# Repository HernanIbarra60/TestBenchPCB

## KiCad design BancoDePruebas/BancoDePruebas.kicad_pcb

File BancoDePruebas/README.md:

# TestBenchPCB
This is a project to design a PCB for measuring the thrust force of a rocket engine.

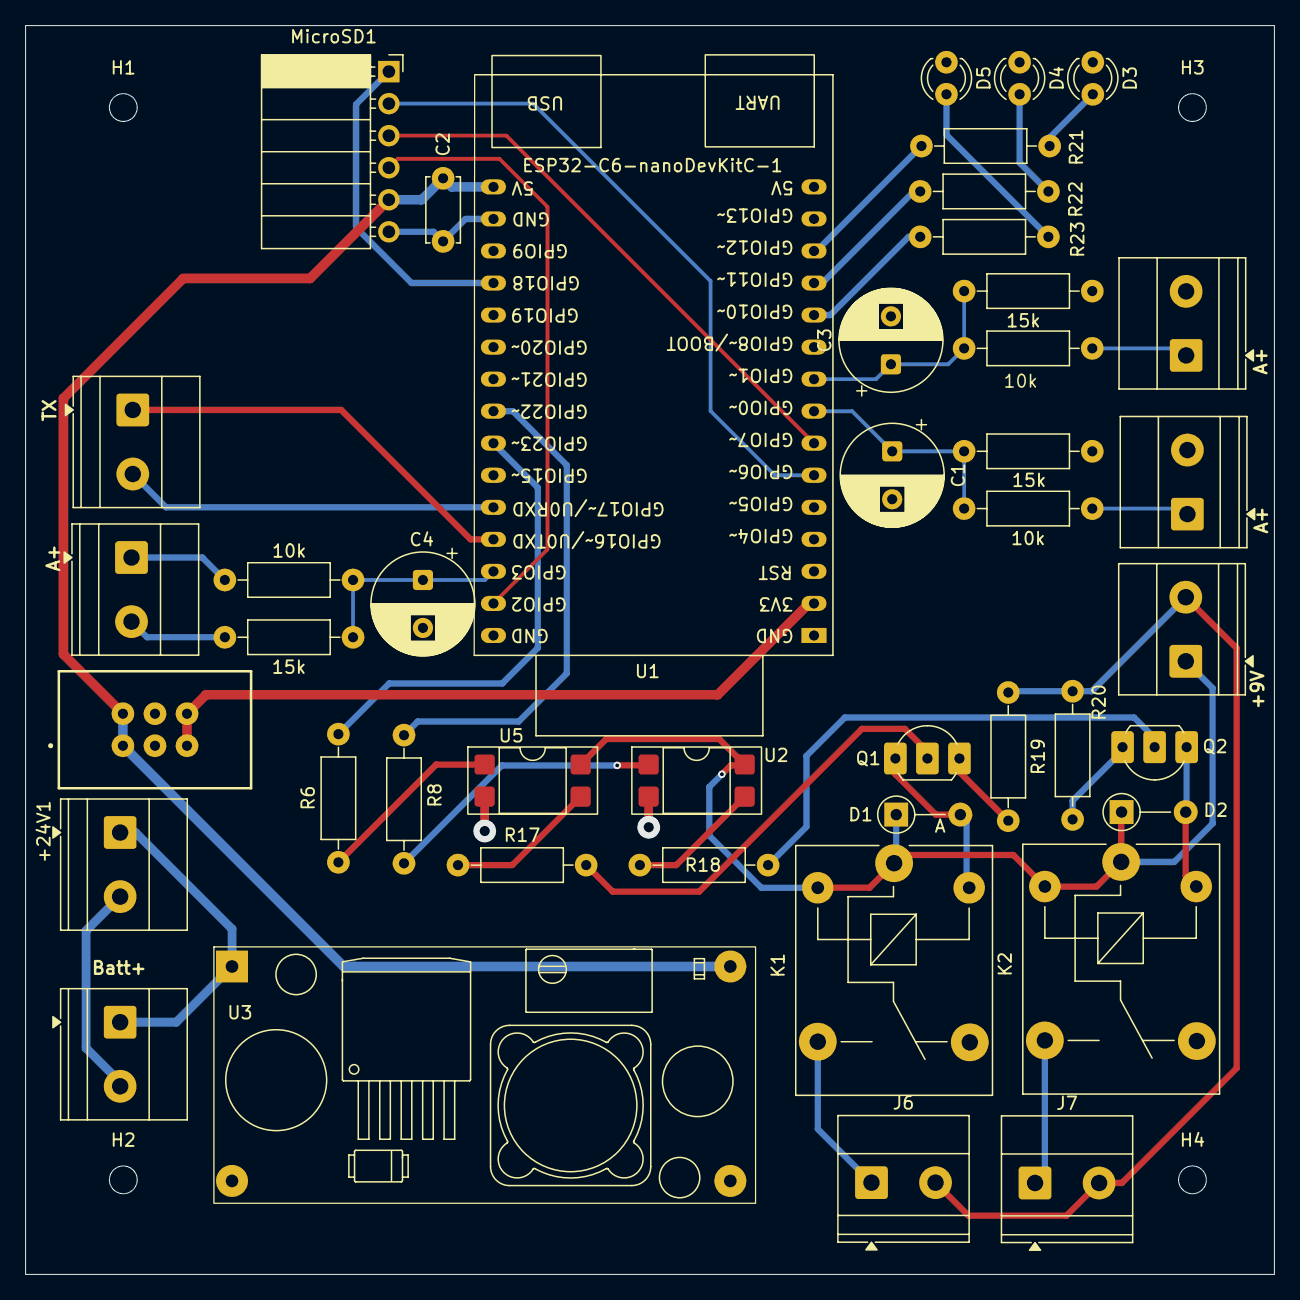
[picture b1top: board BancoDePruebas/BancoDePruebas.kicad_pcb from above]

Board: 2 copper layers, 99.0 x 99.0 mm, 47 parts (0 on the bottom side), 38 nets.

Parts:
10k, 10k#2, 10k#3: 10k; R_Axial_DIN0207_L6.3mm_D2.5mm_P10.16mm_Horizontal_Pad_0.8mm
15k, 15k#2, 15k#3: 15k; R_Axial_DIN0207_L6.3mm_D2.5mm_P10.16mm_Horizontal_Pad_0.8mm
+9V: Screw_Terminal_01x02; TerminalBlock_Phoenix_MKDS-1,5-2-5.08_1x02_P5.08mm_Horizont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
+24V1: BAT; TerminalBlock_Phoenix_MKDS-1,5-2-5.08_1x02_P5.08mm_Horizont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
A+: DAQ2; TerminalBlock_Phoenix_MKDS-1,5-2-5.08_1x02_P5.08mm_Horizont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
A+#2, A+#3: DAQ2; TerminalBlock_Phoenix_MKDS-1,5-2-5.08_1x02_P5.08mm_Horizont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
Batt+: BAT; TerminalBlock_Phoenix_MKDS-1,5-2-5.08_1x02_P5.08mm_Horizont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
C1, C3, C4: C_Polarized; CP_Radial_D8.0mm_P3.80mm
C2: 100nF; C_Disc_D5.0mm_W2.5mm_P5.00mm
D1, D2: D; D_A-405_P5.08mm_Vertical_AnodeUp_Pad_0.5mm
D3: S0; LED_D3.0mm_Pad_0.5mm
D4: S1; LED_D3.0mm_Pad_0.5mm
D5: S2; LED_D3.0mm_Pad_0.5mm
H1, H2, H3, H4: MountingHole; MountingHole_2.2mm_M2
J6: IGN1; TerminalBlock_Phoenix_MKDS-1,5-2-5.08_1x02_P5.08mm_Horizont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
J7: IGN2; TerminalBlock_Phoenix_MKDS-1,5-2-5.08_1x02_P5.08mm_Horizont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
K1, K2: SANYOU_SRD_IGN2; Relay_SPDT_SANYOU_SRD_Series_Form_C
MicroSD1: Conn_01x06; PinSocket_1x06_P2.54mm_Horizontal
Power_output1: Conn_02x03_Odd_Even; SAMTEC_TST-103-01-T-D
Q1, Q2: NPN; TO-92L_Inline_Wide_DIL_Pad
R6, R8: R; R_Axial_DIN0207_L6.3mm_D2.5mm_P10.16mm_Horizontal_Pad_0.8mm
R17, R18: 510; R_Axial_DIN0207_L6.3mm_D2.5mm_P10.16mm_Horizontal_Pad_0.8mm
R19, R20: 1.5; R_Axial_DIN0207_L6.3mm_D2.5mm_P10.16mm_Horizontal_Pad_0.8mm
R21, R22, R23: 220; R_Axial_DIN0207_L6.3mm_D2.5mm_P10.16mm_Horizontal_Pad_0.8mm
TX: DAQ2; TerminalBlock_Phoenix_MKDS-1,5-2-5.08_1x02_P5.08mm_Horizont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
U1: ESP32-C6-nanoDevKitC-1; ESP32-C6-nanoDevkit
U2, U5: PC817; DIP-4_W7.62mm_SMDSocket_SmallPads
U3: DCDC_StepDown_LM2596; YAAJ_DCDC_StepDown_LM2596_chinoka

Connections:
+3V3: Power_output1.5, Power_output1.6, U1.2 (3V3)
+5V: C2.1, MicroSD1.5, Power_output1.1, Power_output1.2, U1.30 (5V), U3.4 (Vout)
+9V: +9V.1, D1.1 (K), D2.1 (K), K1.1, K1.2, K2.1, K2.2, U2.4, U5.4
+BATT: +24V1.1, Batt+.1, U3.1 (Vin)
-BATT: 15k.2, 15k#2.2, 15k#3.2, +24V1.2, A+.2, A+#2.2, A+#3.2, Batt+.2, C1.2, C2.2, C3.2, C4.2, D3.1 (K), D4.1 (K), D5.1 (K), MicroSD1.6, Power_output1.3, Power_output1.4, U1.1 (GND), U1.16 (GND), U1.29 (GND), U2.2, U3.2 (GND), U3.3 (GND), U5.2
A1: 10k.2, 15k#2.1, C1.1, U1.8 (GPIO0)
A1_5v: 10k.1, A+#2.1
A2: 10k#2.2, 15k#3.1, C3.1, U1.9 (GPIO1)
A2_5v: 10k#2.1, A+.1
A3: 10k#3.2, 15k.1, C4.1, U1.18 (GPIO3)
A5_5v: 10k#3.1, A+#3.1
D0_IGN1: R6.1, U1.22 (GPIO23)
D1_IGN2: R8.1, U1.23 (GPIO22)
D2_S2: R23.1, U1.11 (GPIO10)
D3_S1: R22.1, U1.12 (GPIO11)
D4_S0: R21.1, U1.13 (GPIO12)
GND1: +9V.2, J6.2, J7.2, R19.1, R20.1
unnamed: D1.2 (A), K1.5, Q1.1 (C)
unnamed: D2.2 (A), K2.5, Q2.1 (C)
unnamed: D3.2 (A), R21.2
unnamed: D4.2 (A), R22.2
unnamed: D5.2 (A), R23.2
unnamed: J6.1, K1.3
unnamed: J7.1, K2.3
unnamed: Q1.2 (B), R17.2
unnamed: Q1.3 (E), R19.2
unnamed: Q2.2 (B), R18.2
unnamed: Q2.3 (E), R20.2
unnamed: R6.2, U5.1
unnamed: R8.2, U2.1
unnamed: R17.1, U5.3
unnamed: R18.1, U2.3
SPI_CS: MicroSD1.1, U1.27 (GPIO18)
SPI_MISO: MicroSD1.4, U1.17 (GPIO2)
SPI_MOSI: MicroSD1.3, U1.7 (GPIO7)
SPI_SCK: MicroSD1.2, U1.6 (GPIO6)
UART_RX: TX.2, U1.20 (GPIO17)
UART_TX: TX.1, U1.19 (GPIO16)

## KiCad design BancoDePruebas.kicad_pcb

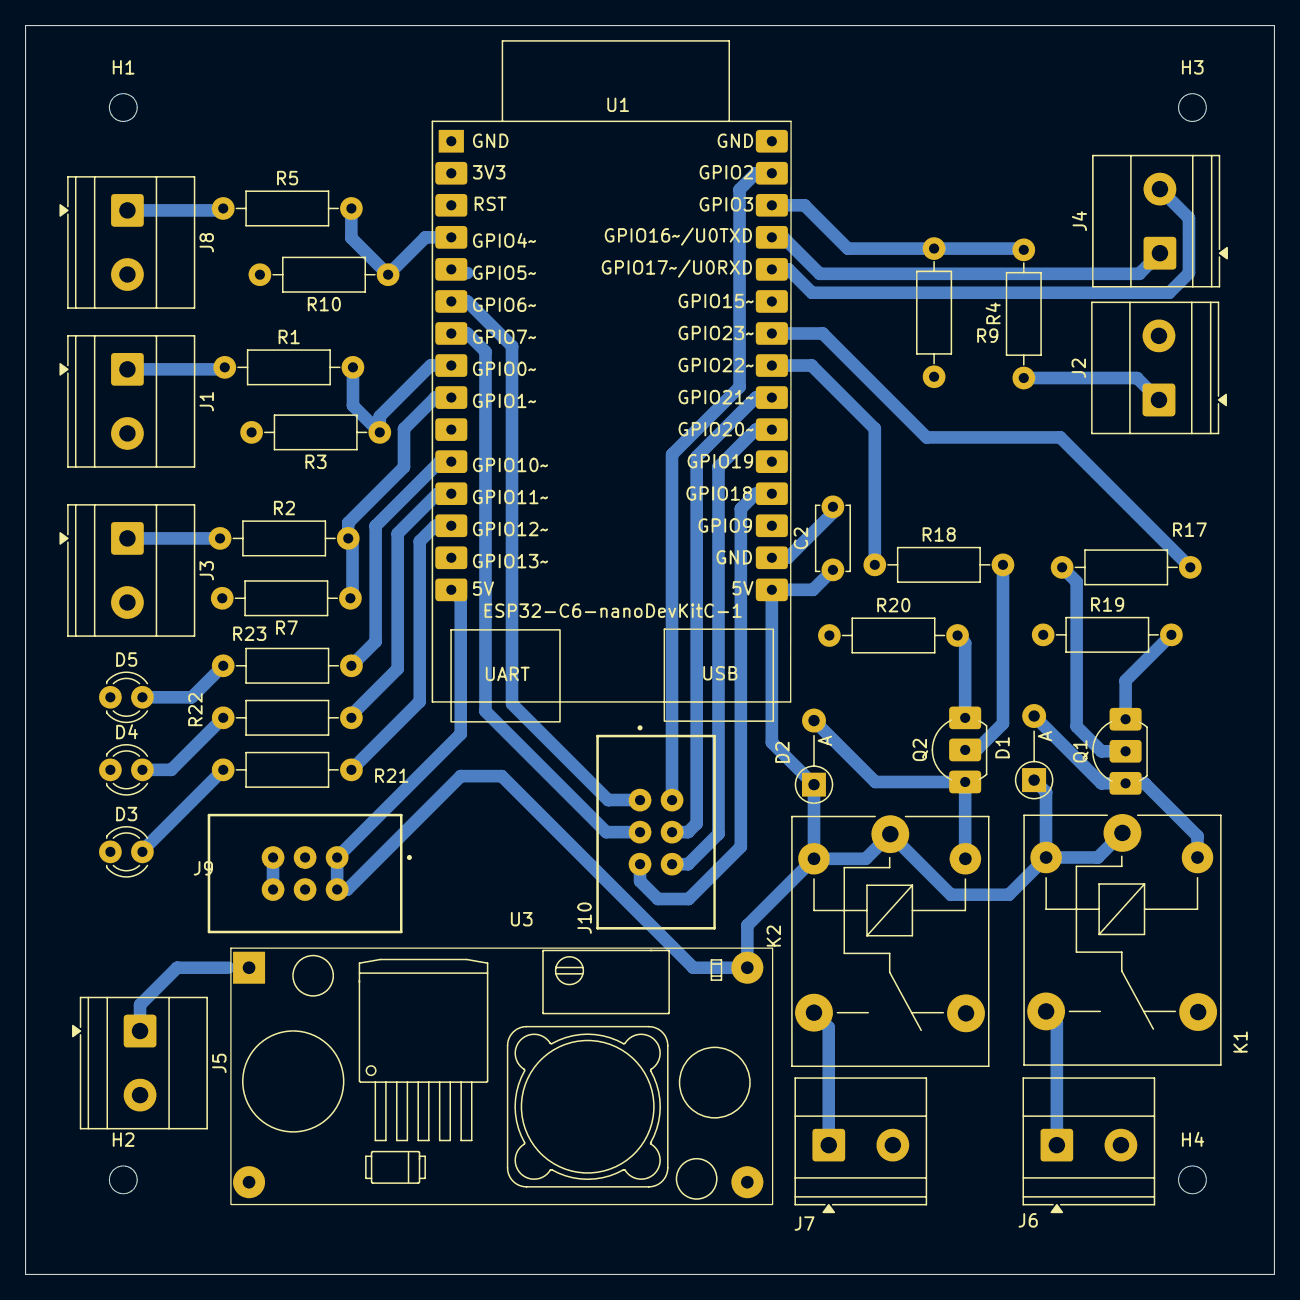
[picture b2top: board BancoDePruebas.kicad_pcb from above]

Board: 2 copper layers, 99.0 x 99.0 mm, 41 parts (0 on the bottom side), 36 nets.

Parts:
C2: 100nF; C_Disc_D5.0mm_W2.5mm_P5.00mm
D1, D2: D; D_A-405_P5.08mm_Vertical_AnodeUp_Pad_0.5mm
D3: S0; LED_D3.0mm_Pad_0.5mm
D4: S1; LED_D3.0mm_Pad_0.5mm
D5: S2; LED_D3.0mm_Pad_0.5mm
H1, H2, H3, H4: MountingHole; MountingHole_2.2mm_M2
J1, J2, J3, J4, J8: DAQ2; TerminalBlock_Phoenix_MKDS-1,5-2-5.08_1x02_P5.08mm_Horizont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
J5: BAT; TerminalBlock_Phoenix_MKDS-1,5-2-5.08_1x02_P5.08mm_Horizont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
J6: IGN1; TerminalBlock_Phoenix_MKDS-1,5-2-5.08_1x02_P5.08mm_Horizont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
J7: IGN2; TerminalBlock_Phoenix_MKDS-1,5-2-5.08_1x02_P5.08mm_Horizont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
J9, J10: Conn_02x03_Odd_Even; SAMTEC_TST-103-01-T-D
K1, K2: SANYOU_SRD_IGN2; Relay_SPDT_SANYOU_SRD_Series_Form_C
Q1, Q2: NPN; TO-92L_Inline_Wide_DIL_Pad
R1, R2, R4, R5: 10k; R_Axial_DIN0207_L6.3mm_D2.5mm_P10.16mm_Horizontal_Pad_0.8mm
R3, R7, R9, R10: 15k; R_Axial_DIN0207_L6.3mm_D2.5mm_P10.16mm_Horizontal_Pad_0.8mm
R17, R18: 510; R_Axial_DIN0207_L6.3mm_D2.5mm_P10.16mm_Horizontal_Pad_0.8mm
R19, R20: 1.5; R_Axial_DIN0207_L6.3mm_D2.5mm_P10.16mm_Horizontal_Pad_0.8mm
R21, R22, R23: 220; R_Axial_DIN0207_L6.3mm_D2.5mm_P10.16mm_Horizontal_Pad_0.8mm
U1: ESP32-C6-nanoDevKitC-1; ESP32-C6-nanoDevkit
U3: DCDC_StepDown_LM2596; YAAJ_DCDC_StepDown_LM2596_chinoka

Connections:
+3V3: J9.5, J9.6
+5V: C2.1, D1.1 (K), D2.1 (K), J9.1, J9.2, K1.1, K1.2, K2.1, K2.2, U1.15 (5V), U1.30 (5V), U3.4 (Vout)
+BATT: J5.1, U3.1 (Vin)
-BATT: C2.2, D3.1 (K), D4.1 (K), D5.1 (K), J1.2, J2.2, J3.2, J5.2, J6.2, J7.2, J8.2, J9.3, J9.4, R3.2, R7.2, R9.2, R10.2, R19.1, R20.1, U1.1 (GND), U1.16 (GND), U1.29 (GND), U3.2 (GND), U3.3 (GND)
A1: R1.2, R3.1, U1.8 (GPIO0)
A1_5v: J1.1, R1.1
A2: R2.2, R7.1, U1.9 (GPIO1)
A2_5v: J3.1, R2.1
A3: R4.2, R9.1, U1.18 (GPIO3)
A4: R5.2, R10.1, U1.4 (GPIO4/MTDI)
A4_5v: J8.1, R5.1
A5_5v: J2.1, R4.1
D0_IGN1: R17.1, U1.22 (GPIO23)
D1_IGN2: R18.1, U1.23 (GPIO22)
D2_S2: R23.1, U1.11 (GPIO10)
D3_S1: R22.1, U1.12 (GPIO11)
D4_S0: R21.1, U1.13 (GPIO12)
D5_RF_CE: J10.4, U1.24 (GPIO21)
D6_RF_IRQ: J10.6, U1.25 (GPIO20)
unnamed: D1.2 (A), K1.5, Q1.1 (C)
unnamed: D2.2 (A), K2.5, Q2.1 (C)
unnamed: D3.2 (A), R21.2
unnamed: D4.2 (A), R22.2
unnamed: D5.2 (A), R23.2
unnamed: J6.1, K1.3
unnamed: J7.1, K2.3
unnamed: Q1.2 (B), R17.2
unnamed: Q1.3 (E), R19.2
unnamed: Q2.2 (B), R18.2
unnamed: Q2.3 (E), R20.2
SPI_CS: J10.5, U1.27 (GPIO18)
SPI_MISO: J10.2, U1.17 (GPIO2)
SPI_MOSI: J10.3, U1.7 (GPIO7)
SPI_SCK: J10.1, U1.6 (GPIO6)
UART_RX: J4.2, U1.20 (GPIO17)
UART_TX: J4.1, U1.19 (GPIO16)

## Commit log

2026-03-09 primer commit
2026-03-09 Add files
